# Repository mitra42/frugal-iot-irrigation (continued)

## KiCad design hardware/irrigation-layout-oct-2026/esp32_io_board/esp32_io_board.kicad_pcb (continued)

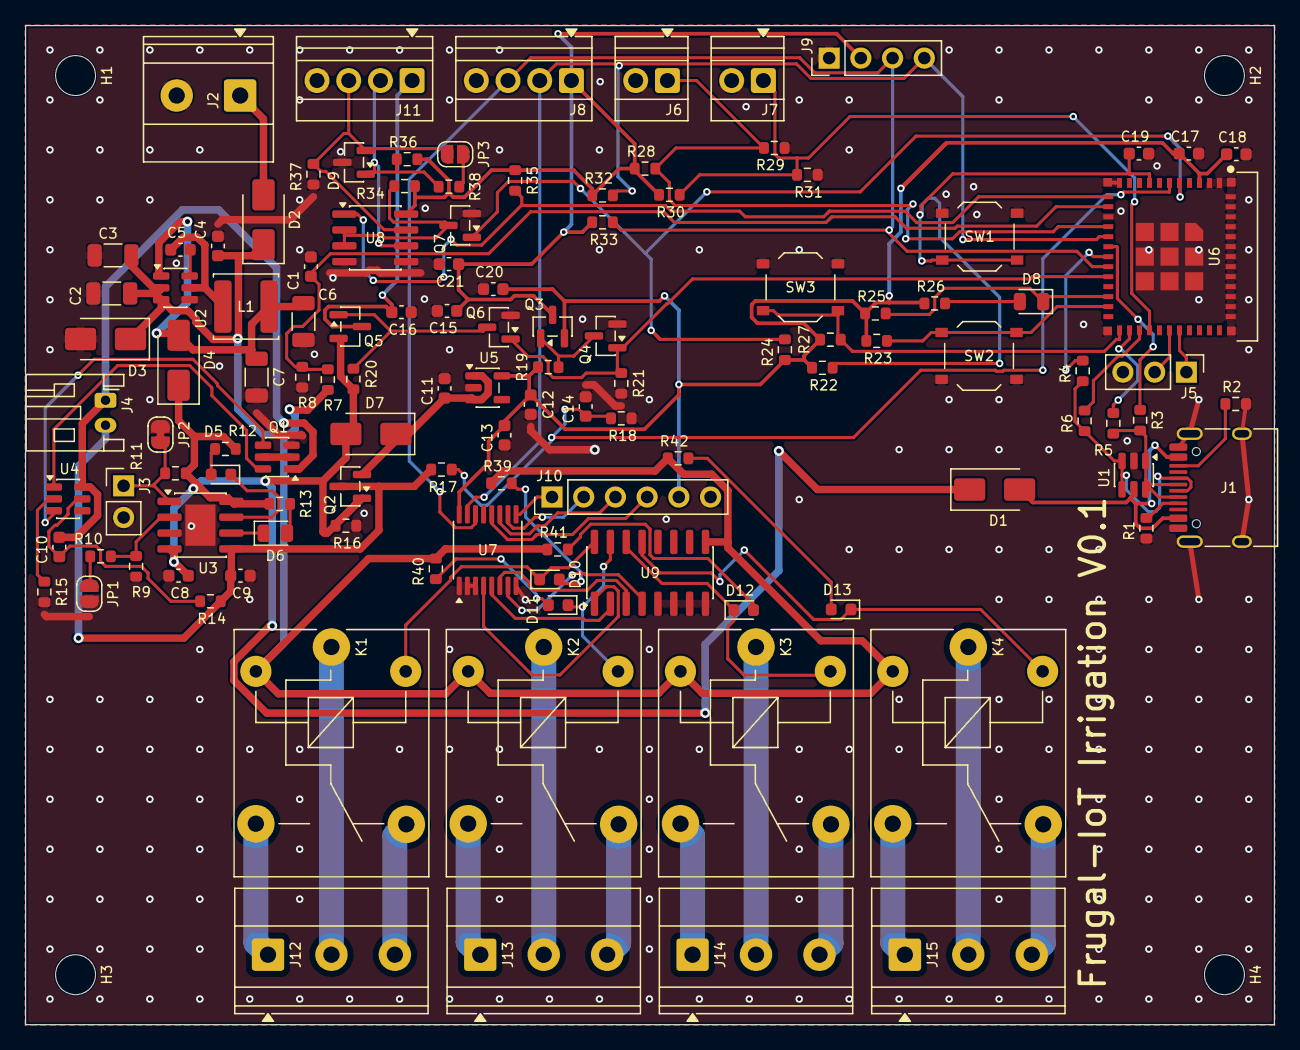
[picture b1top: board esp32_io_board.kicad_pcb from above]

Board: 2 copper layers, 100.0 x 80.0 mm, 122 parts (0 on the bottom side), 84 nets.

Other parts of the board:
H1, H2, H3, H4: M3; MountingHole_3.2mm_M3

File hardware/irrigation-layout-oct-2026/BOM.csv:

"Refs","Value","MPN","LCSC","Footprint","Qty","DNP","Note"
"C1,C4,C5,C10,C13,C14,C18,C20,C21","100nF","100nF","C14663","Capacitor_SMD:C_0603_1608Metric","9","",""
"C2,C3","10uF 25V","10uF 25V","C13585","Capacitor_SMD:C_1206_3216Metric","2","",""
"C6,C7","22uF","22uF","C12891","Capacitor_SMD:C_1206_3216Metric","2","",""
"C8,C9,C11,C12,C16,C17","10uF","10uF","C19702","Capacitor_SMD:C_0603_1608Metric","6","",""
"C15,C19","1uF","1uF","C15849","Capacitor_SMD:C_0603_1608Metric","2","",""
"D1,D2,D4,D7","SS34","SS34","C8678","Diode_SMD:D_SMA","4","",""
"D3","SMAJ15A","SMAJ15A","C19077535","Diode_SMD:D_SMA","1","",""
"D5,D10-D13","RED","KT-0603R","C2286","LED_SMD:LED_0603_1608Metric","5","",""
"D6,D8","GREEN","KT-0805G","C2297","LED_SMD:LED_0805_2012Metric","2","",""
"D9","PSM712","PSM712-LF-T7","C32677","Package_TO_SOT_SMD:SOT-23","1","",""
"J1","USB-C","TYPE-C-31-M-12","C165948","Connector_USB:USB_C_Receptacle_HRO_TYPE-C-31-M-12","1","",""
"J2","12V IN","KF128-5.08-2P","C474952","TerminalBlock_Phoenix:TerminalBlock_Phoenix_MKDS-1,5-2-5.08_1x02_P5.08mm_Horizontal","1","",""
"J3","NTC","NTC","","Connector_PinHeader_2.54mm:PinHeader_1x02_P2.54mm_Vertical","1","DNP",""
"J4","LiPo","S2B-PH-K-S","C157932","Connector_JST:JST_PH_S2B-PH-K_1x02_P2.00mm_Horizontal","1","",""
"J5","UART0 debug","UART0 debug","","Connector_PinHeader_2.54mm:PinHeader_1x03_P2.54mm_Vertical","1","DNP",""
"J6","GPIO_A (C6)","XY308-2.54-2P","C557685","TerminalBlock:TerminalBlock_Xinya_XY308-2.54-2P_1x02_P2.54mm_Horizontal","1","",""
"J7","GPIO_B (C6)","XY308-2.54-2P","C557685","TerminalBlock:TerminalBlock_Xinya_XY308-2.54-2P_1x02_P2.54mm_Horizontal","1","",""
"J8","I2C sensor","XY308-2.54-4P","C915913","TerminalBlock:TerminalBlock_Xinya_XY308-2.54-4P_1x04_P2.54mm_Horizontal","1","",""
"J9","OLED","PZ254V-11-04P","C492403","Connector_PinHeader_2.54mm:PinHeader_1x04_P2.54mm_Vertical","1","",""
"J10","Expander spare","Expander spare","","Connector_PinHeader_2.54mm:PinHeader_1x06_P2.54mm_Vertical","1","DNP",""
"J11","RS485","XY308-2.54-4P","C915913","TerminalBlock:TerminalBlock_Xinya_XY308-2.54-4P_1x04_P2.54mm_Horizontal","1","",""
"J12","Relay 1","KF128-5.08-3P","C474953","TerminalBlock_Phoenix:TerminalBlock_Phoenix_MKDS-1,5-3-5.08_1x03_P5.08mm_Horizontal","1","",""
"J13","Relay 2","KF128-5.08-3P","C474953","TerminalBlock_Phoenix:TerminalBlock_Phoenix_MKDS-1,5-3-5.08_1x03_P5.08mm_Horizontal","1","",""
"J14","Relay 3","KF128-5.08-3P","C474953","TerminalBlock_Phoenix:TerminalBlock_Phoenix_MKDS-1,5-3-5.08_1x03_P5.08mm_Horizontal","1","",""
"J15","Relay 4","KF128-5.08-3P","C474953","TerminalBlock_Phoenix:TerminalBlock_Phoenix_MKDS-1,5-3-5.08_1x03_P5.08mm_Horizontal","1","",""
"JP1","500mA","500mA","","Jumper:SolderJumper-2_P1.3mm_Open_RoundedPad1.0x1.5mm","1","",""
"JP2","NO_NTC","NO_NTC","","Jumper:SolderJumper-2_P1.3mm_Bridged_RoundedPad1.0x1.5mm","1","",""
"JP3","TERM","TERM","","Jumper:SolderJumper-2_P1.3mm_Open_RoundedPad1.0x1.5mm","1","",""
"K1-K4","SRD-12VDC-SL-C","SRD-12VDC-SL-C","C30431","Relay_THT:Relay_SPDT_SANYOU_SRD_Series_Form_C","4","",""
"L1","4.7uH","SWPA5040S4R7NT","C305174","Inductor_SMD:L_Sunlord_SWPA5040S","1","",""
"Q1","FS8205A","FS8205A","C908265","Package_TO_SOT_SMD:SOT-23-6","1","",""
"Q2,Q3,Q5","AO3401A","AO3401A","C15127","Package_TO_SOT_SMD:SOT-23","3","",""
"Q4,Q6,Q7","2N7002","2N7002","C8545","Package_TO_SOT_SMD:SOT-23","3","",""
"R1,R2","5.1k","5.1k","C23186","Resistor_SMD:R_0603_1608Metric","2","",""
"R3,R4","0R","0R","C21189","Resistor_SMD:R_0603_1608Metric","2","","Fit for C6 module"
"R5,R6","0R","0R","C21189","Resistor_SMD:R_0603_1608Metric","2","DNP","Fit for C3 module"
"R7","560k","560k","C23203","Resistor_SMD:R_0603_1608Metric","1","",""
"R8,R16,R19-R21","100k","100k","C25803","Resistor_SMD:R_0603_1608Metric","5","","rails off at reset"
"R9,R10,R32,R33,R39-R42","4.7k","4.7k","C23162","Resistor_SMD:R_0603_1608Metric","8","","with JP: ~500 mA,~250 mA"
"R11,R28-R31","10k","10k","C25804","Resistor_SMD:R_0603_1608Metric","5","DNP","NTC divider, value per cell NTC,pull-down option,pull-up option"
"R12,R13,R15,R26","1k","1k","C21190","Resistor_SMD:R_0603_1608Metric","4","",""
"R14","100R","100R","C22775","Resistor_SMD:R_0603_1608Metric","1","",""
"R17,R18","1M","1M","C22935","Resistor_SMD:R_0603_1608Metric","2","",""
"R22-R25,R27,R34,R35","10k","10k","C25804","Resistor_SMD:R_0603_1608Metric","7","","GPIO8 strap high,also C3 GPIO2 strap high"
"R36,R37","680R","680R","C23228","Resistor_SMD:R_0603_1608Metric","2","","bias"
"R38","120R","120R","C22787","Resistor_SMD:R_0603_1608Metric","1","",""
"SW1","RESET","TS-1187A-B-A-B","C318884","Button_Switch_SMD:SW_Push_1P1T_XKB_TS-1187A","1","",""
"SW2","BOOT / BTN1","TS-1187A-B-A-B","C318884","Button_Switch_SMD:SW_Push_1P1T_XKB_TS-1187A","1","",""
"SW3","BTN2 (C6)","TS-1187A-B-A-B","C318884","Button_Switch_SMD:SW_Push_1P1T_XKB_TS-1187A","1","",""
"U1","USBLC6-2SC6","USBLC6-2SC6","C7519","Package_TO_SOT_SMD:SOT-23-6","1","",""
"U2","AP63205WU","AP63205WU-7","C2071056","Package_TO_SOT_SMD:TSOT-23-6","1","",""
"U3","TP4056","TP4056","C16581","Package_SO:SOIC-8-1EP_3.9x4.9mm_P1.27mm_EP2.41x3.3mm","1","",""
"U4","DW01A","DW01A","C351410","Package_TO_SOT_SMD:SOT-23-6","1","",""
"U5","AP2112K-3.3","AP2112K-3.3","C51118","Package_TO_SOT_SMD:SOT-23-5","1","",""
"U6","ESP32-C6-MINI-1U-H4 (alt C3-MINI-1U)","ESP32-C6-MINI-1U-H4","C20627095","irrigation:ESP32-C3-C6-MINI-1U","1","",""
"U7","TCA9534PWR","TCA9534PWR","C783615","Package_SO:TSSOP-16_4.4x5mm_P0.65mm","1","",""
"U8","SP3485EN","SP3485EN-L/TR","C8963","Package_SO:SOIC-8_3.9x4.9mm_P1.27mm","1","",""
"U9","ULN2003A","ULN2003ADR","C7512","Package_SO:SOIC-16_3.9x9.9mm_P1.27mm","1","",""

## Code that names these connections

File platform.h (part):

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#define ARDUINO_USB_CDC_ON_BOOT 1 // Serial = USB
#define ACTUATOR_LEDBUILTIN_INVERT // status LED D8 on GPIO8 is active LOW
    // --- I2C (sensor terminal J8, OLED header J9, TCA9534) ---
#define I2C_SDA 7
#define I2C_SCL 14
    // --- switched rails: RAIL_EN (GPIO15) HIGH = 3V3_SW and 5V_SW on; 100k pull-down = off at reset.
    // Must be on before ANY I2C traffic - the bus pull-ups are on 3V3_SW - and before RS485.
#define SYSTEM_POWER3v3_PIN 15
    // --- RS485 (J11: 5V_SW, A, B, GND). Direction is switched in hardware from TX, so no DE/RE pin.
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#define SYSTEM_RS485_RX_PIN 0
#define SYSTEM_RS485_TX_PIN 2
#define SYSTEM_RS485_UART Serial1 // Serial is USB, Serial0 is the debug UART
    // --- battery for the LVD interlocks: the 12 V input, V12_SENSE on GPIO1, 560k/100k = x6.6 ---
#define SENSOR_BATTERY_PIN 1
#define SENSOR_BATTERY_VOLTAGE_DIVIDER 6.6
#define SYSTEM_POWER_BAD_READING_MV 9000
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#define IRRIGATION_PUMP_BIT 3 // K4
// #define IRRIGATION_RELAY_INVERT true // only for a relay board that is on when its pin is LOW
    // --- spare inputs ---
// #define SENSOR_TANK_PIN 6 // GPIO_A terminal J6 (ADC1_CH6) - e.g. the tank gauge
    //                                        ; GPIO_B terminal J7 = GPIO22 (digital), BTN2 = GPIO19
    // --- OLED on header J9 (SSD1306 128x64, powered from 3V3_SW) ---
#define ACTUATOR_OLED_WANT
#define ACTUATOR_OLED_IS_SSD1306
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//
// With the ESP32-C3-MINI-1U fitted instead (and R5/R6 fitted, R3/R4 removed - D19):
//   board = esp32-c3-devkitm-1 (4 MB; drop the two board_upload lines), and in the variant and flags:
//   I2C_SDA / OLED_SDA = 10, I2C_SCL / OLED_SCL = 5, SYSTEM_POWER3v3_PIN = 6, UART0 TX/RX = 21/20.
//   No BTN2, GPIO_A or GPIO_B (C6-only pads). The library already inverts the LED for esp32-c3-devkitm-1.
#endif // TODO_ESP32_C6_DEVKITC_1

#ifndef FRUGAL_IOT_BOARD_CONFIGURED
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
